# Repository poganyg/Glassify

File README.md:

# Introduction

We are bringing you a colour-based glass recycling sorter which can separate, in real-time, green, amber and clear bottles!
This is a university project for the subject real-time embedded programming. Watch our short introduction to why and how we are building this project:

<p align="center">
  
</p>

## Motive

Glass is 100% recyclable and by doing so we can substantially reduce raw materials needed, the waste produced as well as water and air pollution.<sup>[1](https://www.glassrecycle.co.uk/Why-Recycle/Facts--Figures/)</sup> However, contamination is a major factor in the effectiveness of recycling.<sup>[2](https://wasterecycling.org/news/426888/NWRA-Celebrates-America-Recycles-Day.htm)</sup> This can be due to non-glass materials disposed alongside with the bottles, such as bottle caps, but also by mixing differently coloured glasses. Colours are achieved by adding impurities, such as sulfur, copper or iron to the glasses. Their purpose is to protect the contents from environmental effects. Even one colour misplaced in the wrong bin can deteriorate the quality of the recycled glass. <sup>[3](https://recyclenation.com/2014/09/recycling-glass-does-color-matter/)</sup> This project aims to achieve a more effective glass recycling to preserve our natural resources and protect our environment. 

## Our Solution

We are presenting here a device which can be installed to recycling points to assisst with the user-side recycling process. Once installed, a single input can be used for the glass recycling bin and the internal sorting would ensure that colour contamination doesn't occur. The device uses a Raspberry Pi microcontroller and is built using 3D printing which means that the overall production cost can be kept under £100. 

<p align="center">
  
</p>

# Have we got your fascination?

To see updates follow us on Facebook, YouTube and Instagram.

If you would like to recreate this project, head over to our [Wiki](https://github.com/poganyg/Glassify/wiki) page where you will find a detailed building guide including a list of all the components you will need for building it. In terms of software requirements, you will need to install:

* [openCV](https://opencv.org/releases.html)
* [Raspicam](http://www.uco.es/investiga/grupos/ava/node/40?fbclid=IwAR3oNeb0COuL_Odd_C1q-Dq5YQPJ6SrulXHsiW9hHNv8-BaiqOYJpjWOB74)
* [WiringPi](http://wiringpi.com/download-and-install/)
* [CMake](https://cmake.org/install/)
* [Git](https://git-scm.com/downloads) (Optional, makes cloning this repository easier.)

Do make sure to only have these installed once on your Raspberry Pi.

To build our software run the following code in your terminal:
```
git clone https://github.com/poganyg/Glassify.git
cd Glassify
mkdir build
cd build
cmake ..
make
```

The project is under the GNU General Public License v3.0.

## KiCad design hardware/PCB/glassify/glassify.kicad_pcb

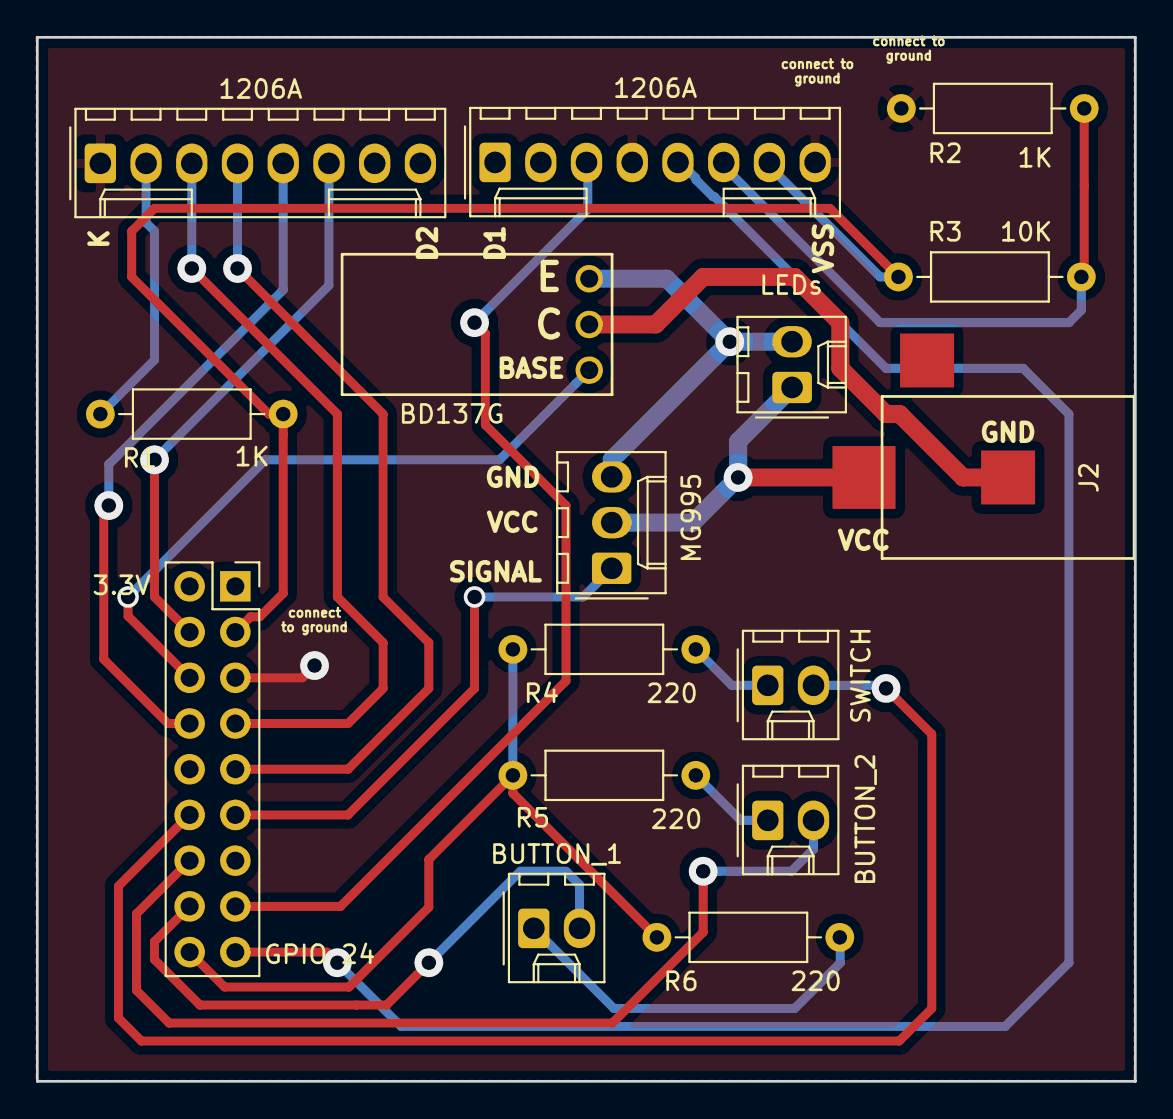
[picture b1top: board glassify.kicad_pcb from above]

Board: 2 copper layers, 61.0 x 58.0 mm, 16 parts (0 on the bottom side), 22 nets.

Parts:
1206A, 1206A#2: 2mm_pitch; Molex_KK-254_AE-6410-08A_1x08_P2.54mm_Vertical
BD137G: ??; BD137G
BUTTON_1: BUTTON_1_OUT; Molex_KK-254_AE-6410-02A_1x02_P2.54mm_Vertical
BUTTON_2: BUTTON_2_OUT; Molex_KK-254_AE-6410-02A_1x02_P2.54mm_Vertical
J1: Conn_02x09_Odd_Even; PinSocket_2x09_P2.54mm_Vertical
J2: Conn_01x03_Male; power_adapter_conn
LEDs: 2mm_pitch; Molex_KK-254_AE-6410-02A_1x02_P2.54mm_Vertical
MG995: MG995_SERVO_OUT; Molex_KK-254_AE-6410-03A_1x03_P2.54mm_Vertical
R1, R2: 1K; R_Axial_DIN0207_L6.3mm_D2.5mm_P10.16mm_Horizontal
R3: 10K; R_Axial_DIN0207_L6.3mm_D2.5mm_P10.16mm_Horizontal
R4, R5, R6: 220; R_Axial_DIN0207_L6.3mm_D2.5mm_P10.16mm_Horizontal
SWITCH: LIMIT_SWITCH_OUT; Molex_KK-254_AE-6410-02A_1x02_P2.54mm_Vertical

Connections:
unnamed: R4.1, SWITCH.1
unnamed: J1.12, SWITCH.2
unnamed: BUTTON_2.1, R5.1
unnamed: BUTTON_2.2, J1.14
unnamed: BUTTON_1.1, R6.1
unnamed: BUTTON_1.2, J1.16
unnamed: J1.11, MG995.1
unnamed: J2.3, LEDs.1, MG995.2
unnamed: BD137G.1, LEDs.2, MG995.3
unnamed: 1206A.1, 1206A#2.4, 1206A#2.8, J1.5, R2.1
unnamed: 1206A.2, R1.1
unnamed: 1206A.3, J1.7
unnamed: 1206A.4, J1.9
unnamed: 1206A.5, J1.8
unnamed: 1206A.6, J1.4
unnamed: 1206A#2.3, J1.15
unnamed: 1206A#2.5, J1.17
unnamed: 1206A#2.6, R2.2, R3.1
unnamed: 1206A#2.7, J1.3, R1.2, R3.2
unnamed: BD137G.2, J2.1
unnamed: BD137G.3, J1.6
unnamed: J1.18, R4.2, R5.2, R6.2

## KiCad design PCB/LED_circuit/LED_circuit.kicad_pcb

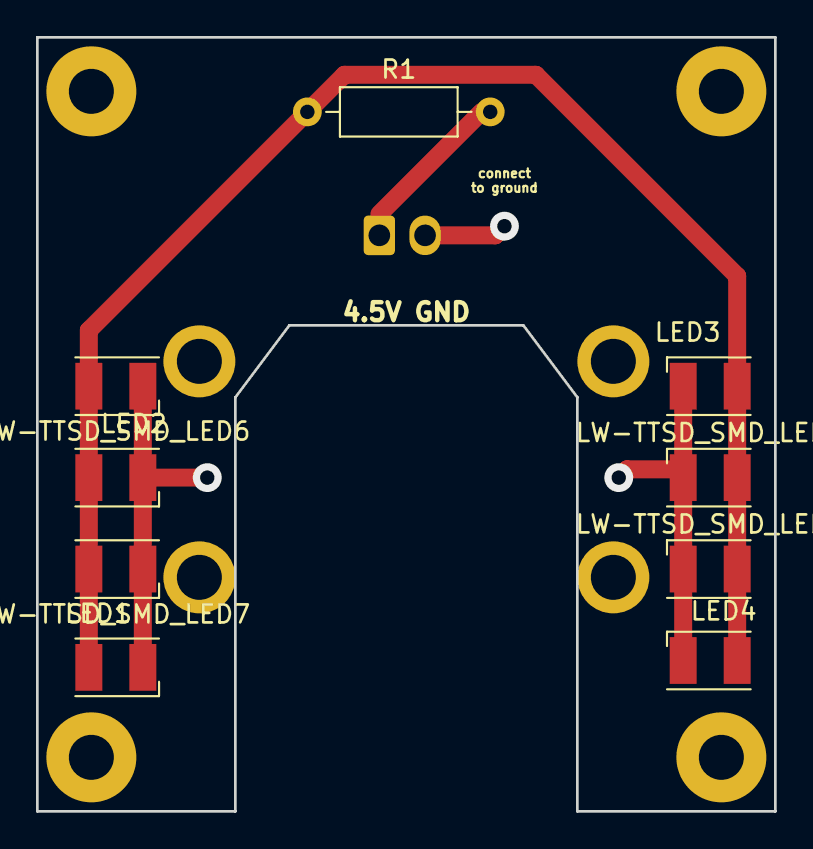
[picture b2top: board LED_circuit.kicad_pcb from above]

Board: 2 copper layers, 41.0 x 43.0 mm, 17 parts (0 on the bottom side), 2 nets.

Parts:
H1, H2, H3, H4, H5, H6, H7, H8: MountingHole; MountingHole_2.5mm_Pad
LED1, LED2, LED3, LED4: 3.2V; LED_PLCC-2
LW-TTSD_SMD_LED5, LW-TTSD_SMD_LED6, LW-TTSD_SMD_LED7, LW-TTSD_SMD_LED8: 3.2V; LED_PLCC-2
R1: 16; R_Axial_DIN0207_L6.3mm_D2.5mm_P10.16mm_Horizontal

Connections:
unnamed: LED1.2, LED2.2, LED3.2, LED4.2, LW-TTSD_SMD_LED5.2, LW-TTSD_SMD_LED6.2, LW-TTSD_SMD_LED7.2, LW-TTSD_SMD_LED8.2, R1.1
unnamed: LED1.1, LED2.1, LED3.1, LED4.1, LW-TTSD_SMD_LED5.1, LW-TTSD_SMD_LED6.1, LW-TTSD_SMD_LED7.1, LW-TTSD_SMD_LED8.1

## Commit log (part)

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2019-02-15 First commit for testing
2019-02-15 adding a directory
2019-02-15 another test
2019-02-20 Renamed to Glassify
2019-02-20 Testing commit function
2019-02-20 "updating"
2019-02-20 "Folder with useful temporary files"
2019-02-22 Add files via upload
    Uploading initial servomotor code
2019-02-22 Add files via upload
    An Alternative servo script
2019-03-08 Renaming Camera folder
2019-03-08 renaming directory again
2019-03-08 Adding the servo files folder
2019-03-08 testing servo motors
2019-03-08 servos
2019-03-08 added missing header file to allow it to run
2019-03-08 First attempt at class for image acquisition
2019-03-08 adding a simple script to test the camera class
2019-03-08 fixed various mistyped errors
2019-03-08 Fixed various typos
2019-03-08 altered to functional state by removing -1 output
2019-03-08 semicolons and such altered
2019-03-15 Added camera setup and camera burst functionality
2019-03-15 Removing unnecessarily commited folder
2019-03-15 Updates to and recovery of camera class
2019-03-15 OpenCV test file
2019-03-15 Resolved merge conflict
2019-03-15 Resolving various syntax errors
2019-03-15 Further syntax corrections to class
2019-03-16 Adding the Display Testing folder
2019-03-16 Testing the display of button messages on the LCD screen
2019-03-16 Testing the buttons display on the LCD screen
2019-03-16 Minor fixes
2019-03-18 removing erronous reference to "time"
2019-03-18 Added code to operate the transistor switch
2019-03-18 removing returned values in void function
2019-03-18 testing the LED
2019-03-18 keeping GPIO pin high
2019-03-18 testing GPIO LED
2019-03-18 Added name cycling functionality to burst function
2019-03-19 Adding beginnings of classification method
2019-03-20 testing opencv with raspicam
2019-03-20 further modifications to opencv/raspicam test
2019-03-20 New script to convert unsigned chars to Mat
2019-03-20 Converting Char2Mat to a class
2019-03-20 in progress of converting uchar to Mat
2019-03-20 Demo of display for social media
2019-03-21 Testing out the new circuit setup
2019-03-21 fixing a minor bug
2019-03-21 Converting function names so they don't match and saving with open cv
2019-03-21 Altered to fully compilable state, added testing outputs
2019-03-25 Uploading cpp class for controlling servos with PWM
2019-03-25 Debugging raspberry pi opencv
2019-03-25 debugging opencv on raspberry pi
2019-03-26 Adding functioning motor class for our specific setup
2019-03-27 OpenCV working
2019-03-27 Pathing and syntax changes, now fully functional
2019-03-27 Tidying and making working class
2019-03-27 Updating changes to camera class
2019-03-29 Implemented CMake for compiling of scripts for operation of motors, see: IndependentMotors
2019-03-29 Removing folders no longer needed for operation of motors as all required is contained within 'IndependentMotors'
2019-03-29 Adding provisional hardware models
2019-03-29 Adding the preliminary PCB designs
2019-03-29 Moved contents of 'IndependentMotors' into 'Motors' as no longer need sub-directory
2019-03-29 Added Processing.h to enable control over camera settings and HSV image processing.
2019-03-30 Added working classification method
    Working classification scheme implemented, simplifying previous version and ready for implementation on raspberry pi
2019-03-30 Changed output to pixel counts, added brown
    Rewrote script to give pixel count outputs, rather than Mat objects
    Added brown as another output in addition to green and clear.
2019-03-31 Uploading second generation of hardware models
2019-03-31 Added working script "ClassifyPi.h" for distinguishing clear/brown/green bottles
2019-03-31 Adding remaining hardware models
    Added remaining hardware models, as well as externally sourced reference designs for gear and servo motor.
2019-03-31 Adding some hardware STLs
2019-03-31 Added C++ LCD control, compiling with CMake. Moved python examples into new folder.
2019-04-01 Added primitive doxygen files for camera/image classification
2019-04-01 Moving traces further from edges, moving some traces from top layer to bottom one.
2019-04-02 Adding better-toleranced CAD models. Redesigned ServoCarriage.
2019-04-02 Added LEDs to have the option of installing more if needed, fixed ground layer on main board to be connected everywhere, rewired pins to ease soldering
2019-04-02 Simple script to test classes on hardware
2019-04-02 Added two more drill guides and updated STLs
    Drill Guide added for the join between 100mm halfpipe and rotating portion
    Drill guide for join between two 120mm pipes added
    Added remaining .STL files for new parts and remaining SLDPRT files
2019-04-02 Replaced manually-created functions with OpenCV funcs.
    Replaced manually-created HSV thresholding functions with cv::inRange() functions
2019-04-03 Added working unit test structure for further development
2019-04-04 Added Provisional.h, more efficient & object-oriented
    Script contains a more efficient and object-oriented approach to creating the camera class and performing classification
2019-04-04 Adding a ground plane to the front of the board too.
2019-04-04 Removing unnecessary folders and updating new Provisional.h class
2019-04-04 Removing need for unreliable ServoControl class
2019-04-04 Fixing the distance between drilling holes on the LED board
2019-04-04 fixing backside gnd layer
2019-04-04 Adding threading scripts to thread classification
2019-04-05 Readjusting the locations of the drill holes again.
2019-04-05 Classes threaded for more efficient use
2019-04-05 Output from classification now accessable by main
2019-04-05 Resolved issues with Motor class communication
2019-04-05 First half of electronics housing
2019-04-05 Resolved issues preventing switch polingd
2019-04-05 Switch script releases pin and works with motor
2019-04-05 Adding all required libraries to appropiate folder
2019-04-06 Added provisional electronics housing cover
    Added provisional electronics housing cover. Only slight altering of dimensions necessary once dimensions of LCD, battery pack & buttons are obtained
2019-04-06 Resolved lack of looping- still functions
2019-04-06 Adding classification files to test on Pi
2019-04-06 Editing the C script used to display text on the display for it to work with the pins on the PCB board.
2019-04-06 Added *ALMOST* functional classification script
2019-04-07 Improved thresholding routine for the classifier
2019-04-07 Functioning synchronised classification and sorting
2019-04-08 Changes dimensions of connection to servo
    Changed servo gear dimensions to allow more snug fit to servo motor and screw
2019-04-08 Adding STLs of test gears
    Adding STLs of test gears for the servo motor
2019-04-08 Added bolt-guard for outlet pipe
2019-04-09 Added BoldGuard STL
2019-04-09 Adjustments for Audio/HDMI/LCD
    Adjustments for Audio jack, HDMI port and LCD screen on the electronics housing
2019-04-09 Adding a cover photo for the Readme
2019-04-09 Adding a cover photo for the Readme.
2019-04-09 Removing as a better version of is available
2019-04-09 Switch holder added
2019-04-09 Created sorter stand
2019-04-09 dditional test sizes for servo gear
2019-04-10 Adding altered classification and motor scripts to test on Pi
2019-04-10 Updating the Readme
2019-04-10 Increased bolt-top diameter on Stand
2019-04-10 Updated Threaded_Classes to use CMake from separate directory. Made Servo object separate from Threads.
2019-04-10 Created Independent Camera Class
2019-04-10 Removing no-longer-needed files/folders: Testing_Camera, Classification. Moved PCD and 3D model files into 'hardware'.
2019-04-10 Enabling testing on CMakeLists.txt
2019-04-11 Updated Electronics casing to fit RPi and new LED PCB
2019-04-11 Menu can now scroll and read motor angle
2019-04-11 Motor moves live as settings changed
2019-04-11 Parallelising classification
2019-04-11 Splitting Camera class into Classifier and Camera
2019-04-11 Saving and loading the calibration values in the libServo file.
2019-04-11 Committing Changes to unified script. Compiles as tested.
2019-04-11 Added links to required packages
2019-04-11 Embedded link to youtube summary video
2019-04-12 LCD working within Menu script. Still need Class for display.
2019-04-12 LCD display now integrated through a class
2019-04-12 Added thread for classification
2019-04-12 Modified state class to possess a buffer for bottles
2019-04-12 Edited SwitchThread to increase buffer within State Class on trigger
2019-04-12 Making Menu class, object-oriented
2019-04-12 Added thread to poll after the original thread has triggered
2019-04-12 Updated CMakeLists for linking wiringPi libraries. Edited main script and includes for successful compile.
2019-04-12 Adding buffer-usage functionality to classification routine
2019-04-12 Reverting to allow branching at this point to a more experimental branch.
    Revert "Adding buffer-usage functionality to classification routine"
    This reverts commit 60cce25d2b257a27df5b04b0ea969c78c1aa961d.
2019-04-12 Added buffer functionality to State class
2019-04-12 Updated Classifier to utilise buffer
2019-04-12 Adapted MotorThread to utilise buffer functionality, altered lowering of buffer in Classifier to accommodate.
2019-04-13 Functionalised Menu
2019-04-13 Image files for wiki and updated switch casing
2019-04-13 Functioning object orianted menu.
2019-04-13 Electronics Cover Completed
2019-04-13 Adding centered images with links and finalising the content
2019-04-13 Adding cropped schematic and pcd layout images
2019-04-13 Updated classification to work on one thread -- works well.
2019-04-13 Merged Menu and began assimilating menu into script
2019-04-14 Added doxygen comments to switchthread and libServo
2019-04-14 Integrated Menu into main function, added Menu thread. Still to be tested.
2019-04-14 Added tests of the camera functionality.
2019-04-14 Updated camera test
2019-04-14 Doxygen comments added throughout
2019-04-14 Made changes to libServo.cpp and libServo.h for more effective unit testing
2019-04-14 Added provisional tests for Servo and Display classes
2019-04-14 Added Unit test for State class. Uses threads to test mutex.
2019-04-14 Amended StateTestThread.cpp
2019-04-14 Modifying Classifier.h to simplify testing
2019-04-14 Altered doxygen comments on Classifier.h
2019-04-14 Adding cropped PCB layout images
2019-04-14 Updating cropped images
2019-04-14 Added tests for the Classifier class
2019-04-14 Edited Camera to contain Mat conversion of image data. Edited Classifier to reflect this.
2019-04-14 further doxygen documntation comments added
2019-04-14 Corrected camera test to reflect recent changes to source files
2019-04-14 Added class descriptions
2019-04-14 Added beginnings of menu test. Separate class for buttons would make it much easier to test.
2019-04-14 adding converted Gantt im
2019-04-14 Corected doxygen notation
2019-04-14 Renamed test and updated cmakelists
2019-04-14 Removed errors from files
2019-04-14 Corrected doxygen notation
2019-04-14 Doxygen and indentation
2019-04-14 Tidied up CMakeLists
2019-04-14 Doxygen touch up to resolve errors
2019-04-15 Modified CMakeLists for Unit Tests
2019-04-15 Initial commit of the doxygen files
2019-04-15 Adding images for the wiki
2019-04-15 Adding Unit Tests
2019-04-15 Adding further unit tests to CMakeLists
2019-04-15 Most tests uploaded. Debugging still required.
2019-04-15 Adding the assembly guide
2019-04-15 Menu now works within the main script
2019-04-15 Modification to camera test
2019-04-15 Ammended testing script for Display. Others remain.
2019-04-15 Adapted CMakeLists to create test executables in test folder.
2019-04-15 Removed redundant test "MatConvert.cpp"
2019-04-15 All implemented tests working. Edited Classifier.
2019-04-15 Adding install instructions and centered images
2019-04-15 Separated Menu class into Menu and Buttons classes
2019-04-15 Adder *nearly* working menu tests.
2019-04-15 Final update to hardware - PCBs & Datasheets
2019-04-15 Debugged device. Fully functional.
2019-04-15 Further calibrated device
2019-04-15 updating the installation instructions
2019-04-15 Updating the Doxygen files and the assembly guide
